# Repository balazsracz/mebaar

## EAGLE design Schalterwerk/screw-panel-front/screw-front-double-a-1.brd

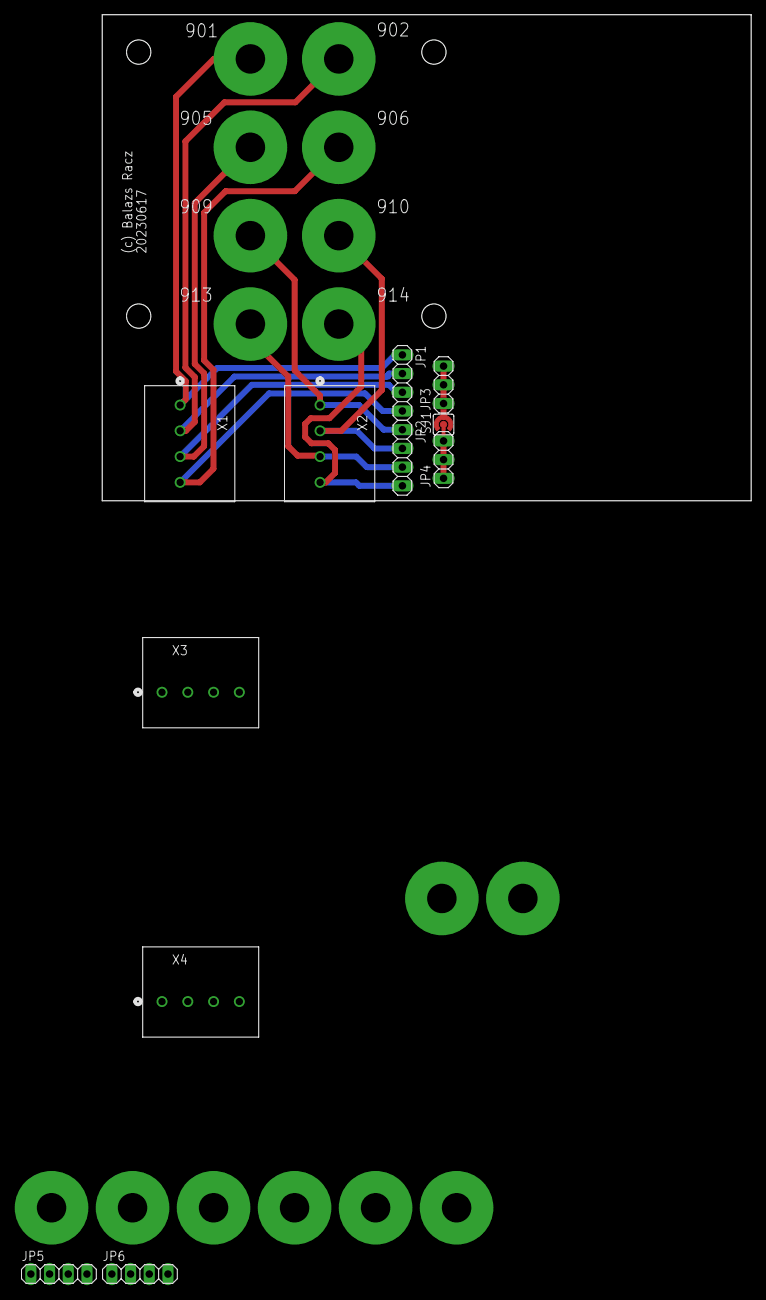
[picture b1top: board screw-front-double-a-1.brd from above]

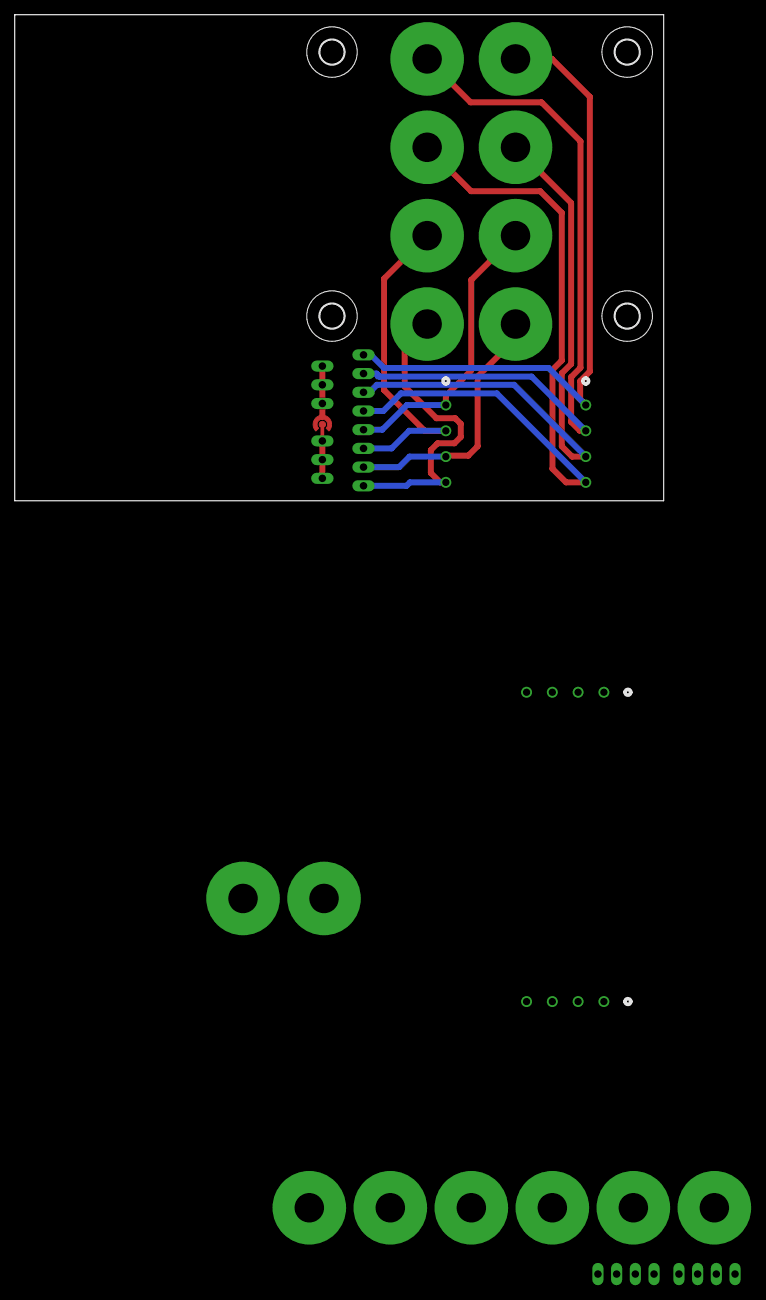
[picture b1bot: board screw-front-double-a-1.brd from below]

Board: 2 copper layers, 88.1 x 66.0 mm, 31 parts (4 on the bottom side), 18 nets.

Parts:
H1, H2, H3, H4: MOUNT-HOLE3.3; 3,3
J1, J2, J3, J4, J5, J6, J7, J8, J9, J10, J11, J12, J13, J14, J15, J16: M4-SCREW-HOLE
JP1, JP2, JP5, JP6: 1X04
JP3, JP4: 1X03
SJ1: SJ_RND2
X1, X2, X3, X4: PHNX_4P_350CONN_1984989_PXC; PHNX_4P_350

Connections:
unnamed: J1.P$1, JP1.1, X1.1
unnamed: J2.P$1, JP1.2, X1.2
unnamed: J3.P$1, JP1.3, X1.3
unnamed: J4.P$1, JP1.4, X1.4
unnamed: J5.P$1, JP2.1, X2.1
unnamed: J6.P$1, JP2.2, X2.2
unnamed: J7.P$1, JP2.3, X2.3
unnamed: J8.P$1, JP2.4, X2.4
unnamed: JP3.1, JP3.2, JP3.3, SJ1.P$2
unnamed: JP4.1, JP4.2, JP4.3, SJ1.P$1
unnamed: J9.P$1, JP5.1, X3.1
unnamed: J10.P$1, JP5.2, X3.2
unnamed: J11.P$1, JP5.3, X3.3
unnamed: J12.P$1, JP5.4, X3.4
unnamed: J13.P$1, JP6.1, X4.1
unnamed: J14.P$1, JP6.2, X4.2
unnamed: J15.P$1, JP6.3, X4.3
unnamed: J16.P$1, JP6.4, X4.4

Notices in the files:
parts and their libraries:
COPYRIGHT: Copyright (C) 2023 Ultra Librarian. All rights reserved.
